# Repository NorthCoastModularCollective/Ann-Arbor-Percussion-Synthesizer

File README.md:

# Ann Arbor Percussion Synthesizer

A module that generates “abstract” percussion sounds and has a fairly simple interface. It won’t be intended to create “bass drums” or “snares” or “hi hats”, though it’ll probably be able to make things that approximate those sounds. It is raw, dirty, glitchy, lo-fi, and abstract. A Banksy interpretation of a Dali painting of industrial-steam-punk-Qbert. Interacting with it gives you a feeling of exploration and discovery with little emphasis on predictability and reproducibility. However, great care was taken to make the experience not feel like pure chaos and randomness. 

CAUTION: this project is still in development. There are many bugs and gaps. 

Audio Sample, [here](https://soundcloud.com/verzerren/ann-arbor-percussion-synthesizer-v-001-sound-sample)

https://github.com/NorthCoastModularCollective/Ann-Arbor-Percussion-Synthesizer/assets/6989685/e6aa8b81-97f8-49d5-8cca-bbeed19dbfc6

Hardware Overview:
- Teensy 4.1
- Teensy Audio Library
- Eurorack Trigger/Gate input

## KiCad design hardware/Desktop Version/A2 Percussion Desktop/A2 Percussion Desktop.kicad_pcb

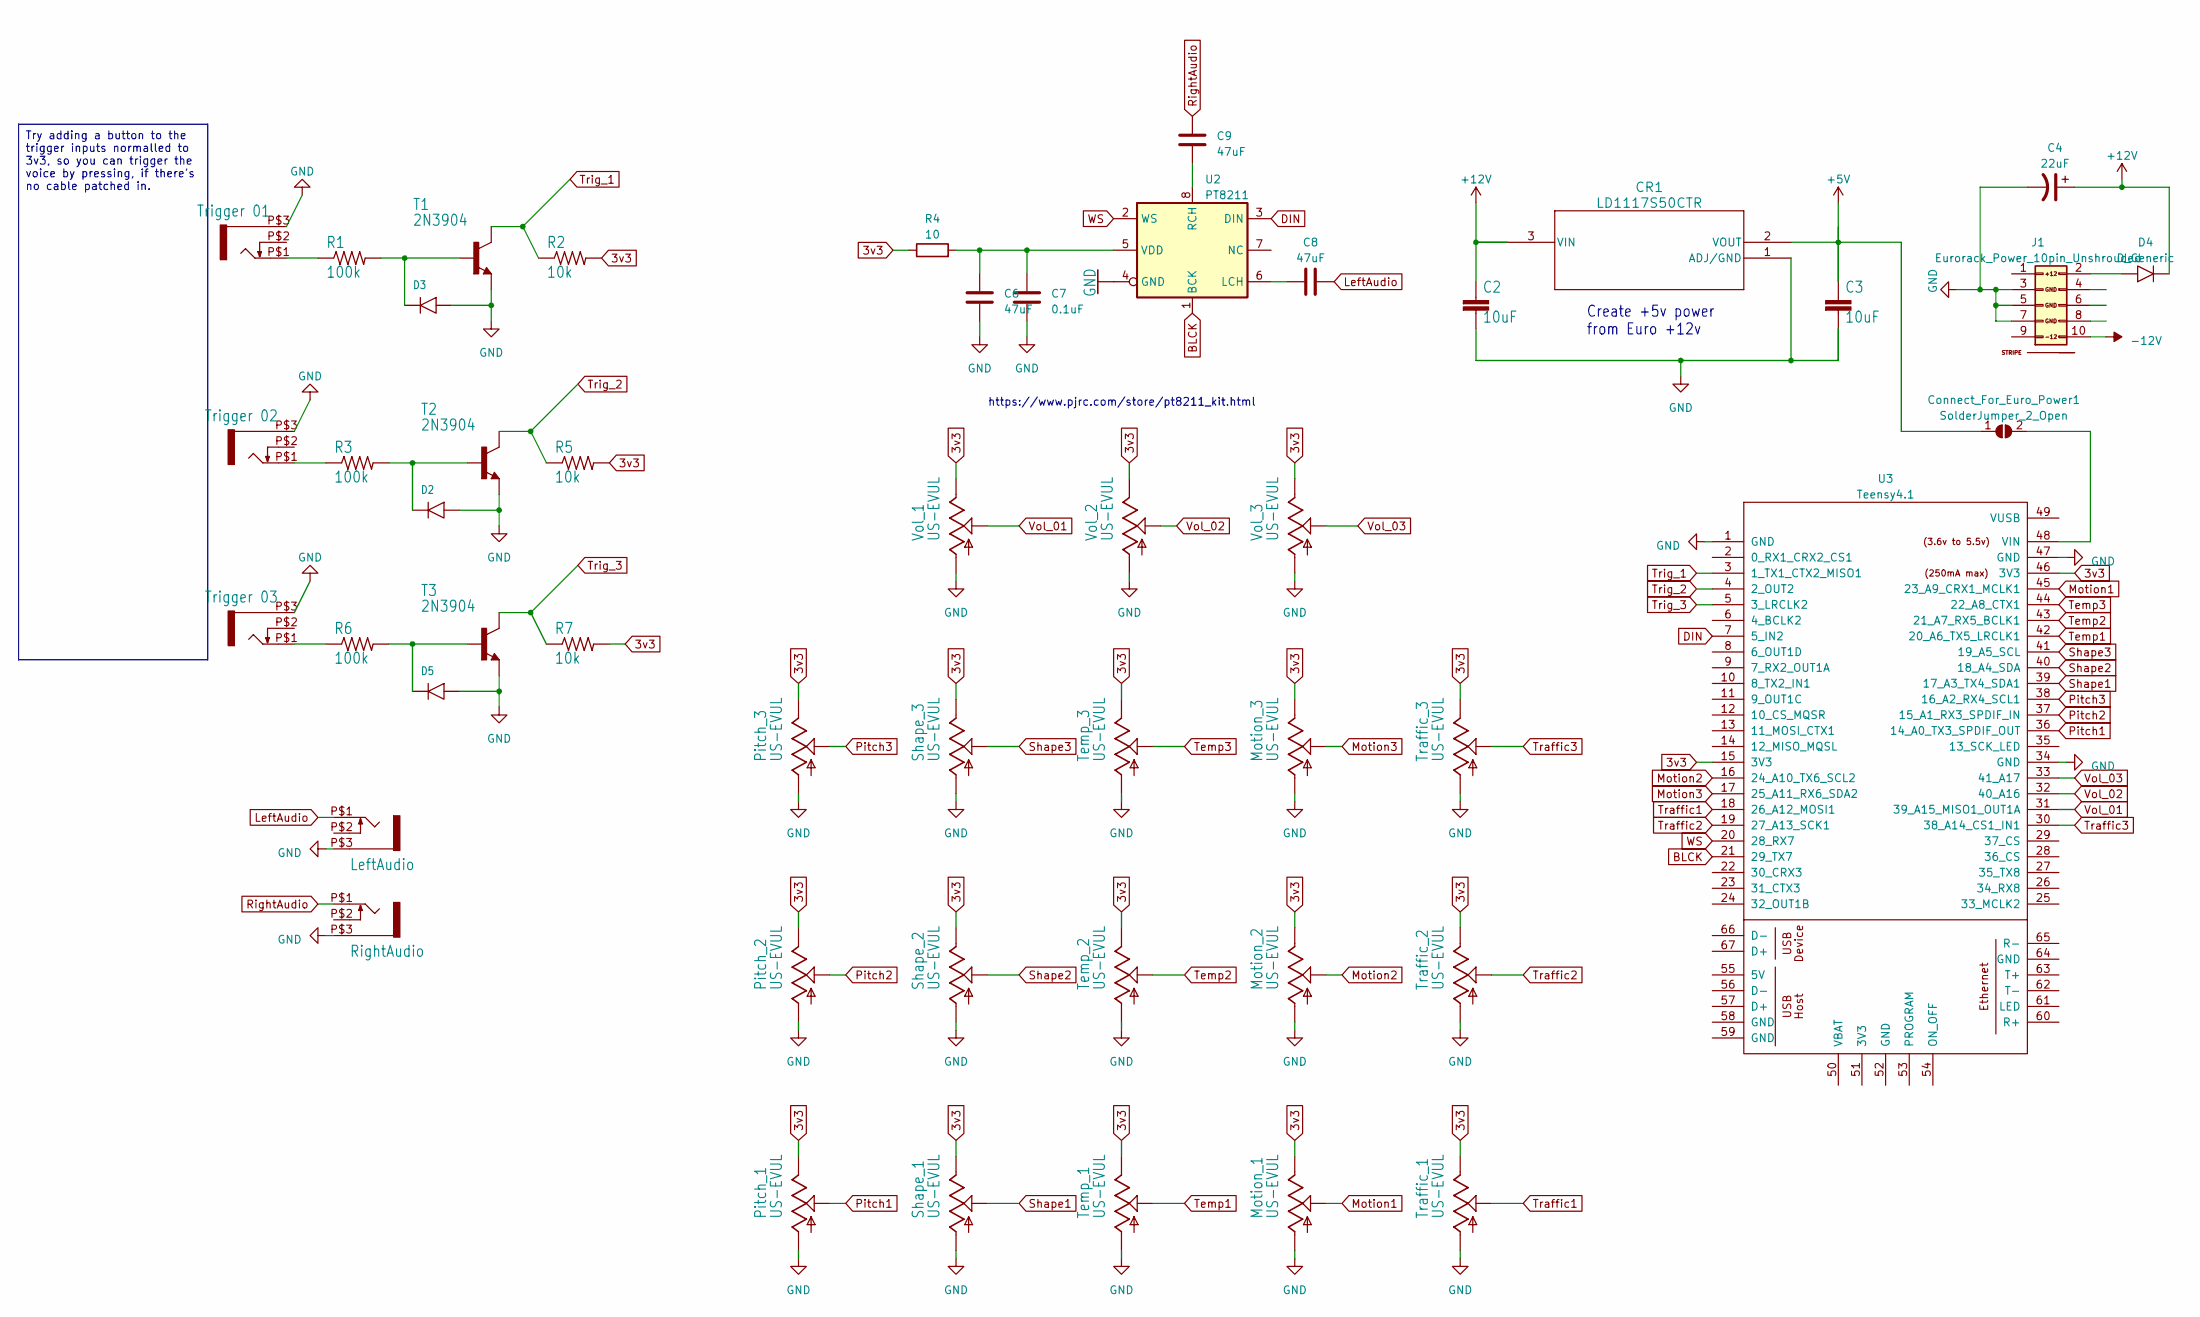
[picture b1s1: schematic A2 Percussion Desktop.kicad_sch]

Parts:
C2, C3: 10uF; C_Disc_D4.3mm_W1.9mm_P5.00mm
C4: 22uF; CP_Radial_D5.0mm_P2.50mm
C6, C8, C9: 47uF; C_Axial_L5.1mm_D3.1mm_P7.50mm_Horizontal
C7: 0.1uF; C_Axial_L5.1mm_D3.1mm_P7.50mm_Horizontal
CR1: LD1117S50CTR; SOT-223_STM
Connect_For_Euro_Power1: SolderJumper_2_Open; JUMPER_SMD_1x2
D2, D3, D5: DIODESOD-123; D_DO-35_P7.62mm_Horizontal
D4: D_Generic; D_DO-35_P7.62mm_Horizontal
J1: Eurorack_Power_10pin_Unshrouded; Pins_2x05_2.54mm_TH_Europower; Part Number 1-1002FBV0T
LeftAudio1: LeftAudio; WQP-PJ301M-12_JACK
Motion_1, Motion_2, Motion_3: US-EVUL; EVUFXL
Pitch_1, Pitch_2, Pitch_3: US-EVUL; EVUFXL
R1, R3, R6: 100k; R_Axial_DIN0207_L6.3mm_D2.5mm_P7.62mm_Horizontal
R2, R5, R7: 10k; R_Axial_DIN0207_L6.3mm_D2.5mm_P7.62mm_Horizontal
R4: 10; R_Axial_DIN0207_L6.3mm_D2.5mm_P7.62mm_Horizontal
RightAudio1: RightAudio; WQP-PJ301M-12_JACK
Shape_1, Shape_2, Shape_3: US-EVUL; EVUFXL
T1, T2, T3: 2N3904; TO92
TRIG1: Trigger 01; WQP-PJ301M-12_JACK
TRIG2: Trigger 02; WQP-PJ301M-12_JACK
TRIG3: Trigger 03; WQP-PJ301M-12_JACK
Temp_1, Temp_2, Temp_3: US-EVUL; EVUFXL
Traffic_1, Traffic_2, Traffic_3: US-EVUL; EVUFXL
U2: PT8211; VSSOP-8_3.0x3.0mm_P0.65mm
U3: Teensy4.1; Teensy41
Vol_1, Vol_2, Vol_3: US-EVUL; EVUFXL

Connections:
3v3: Motion_1.3 (E), Motion_2.3 (E), Motion_3.3 (E), Pitch_1.3 (E), Pitch_2.3 (E), Pitch_3.3 (E), R2.2, R4.1, R5.2, R7.2, Shape_1.3 (E), Shape_2.3 (E), Shape_3.3 (E), Temp_1.3 (E), Temp_2.3 (E), Temp_3.3 (E), Traffic_1.3 (E), Traffic_2.3 (E), Traffic_3.3 (E), U3.15 (3V3), U3.46 (3V3), Vol_1.3 (E), Vol_2.3 (E), Vol_3.3 (E)
+5V: C3.1, CR1.2 (VOUT), Connect_For_Euro_Power1.1 (A)
+12V: C2.1, C4.1, CR1.3 (VIN), D4.1 (K)
-12V: J1.10 (-12V)
BLCK: U2.1 (BCK), U3.21 (29_TX7)
DIN: U2.3 (DIN), U3.7 (5_IN2)
GND: C2.2, C3.2, C4.2, C6.2, C7.2, CR1.1 (ADJ/GND), D2.2 (A), D3.2 (A), D5.2 (A), J1.3 (GND), J1.5 (GND), J1.7 (GND), LeftAudio1.P$3 (1), Motion_1.1 (A), Motion_2.1 (A), Motion_3.1 (A), Pitch_1.1 (A), Pitch_2.1 (A), Pitch_3.1 (A), RightAudio1.P$3 (1), Shape_1.1 (A), Shape_2.1 (A), Shape_3.1 (A), T1.3 (E), T2.3 (E), T3.3 (E), TRIG1.P$3 (1), TRIG2.P$3 (1), TRIG3.P$3 (1), Temp_1.1 (A), Temp_2.1 (A), Temp_3.1 (A), Traffic_1.1 (A), Traffic_2.1 (A), Traffic_3.1 (A), U2.4 (GND), U3.1 (GND), U3.34 (GND), U3.47 (GND), Vol_1.1 (A), Vol_2.1 (A), Vol_3.1 (A)
LeftAudio: C8.2, LeftAudio1.P$1 (2)
Motion1: Motion_1.2 (S), U3.45 (23_A9_CRX1_MCLK1)
Motion2: Motion_2.2 (S), U3.16 (24_A10_TX6_SCL2)
Motion3: Motion_3.2 (S), U3.17 (25_A11_RX6_SDA2)
unnamed: Connect_For_Euro_Power1.2 (B), U3.48 (VIN)
unnamed: D2.1 (K), R3.2, T2.2 (B)
unnamed: D3.1 (K), R1.2, T1.2 (B)
unnamed: D4.2 (A), J1.2 (+12V)
unnamed: D5.1 (K), R6.2, T3.2 (B)
unnamed: R1.1, TRIG1.P$1 (2)
unnamed: R3.1, TRIG2.P$1 (2)
unnamed: R6.1, TRIG3.P$1 (2)
unnamed: C8.1, U2.6 (LCH)
unnamed: C9.1, U2.8 (RCH)
unnamed: C6.1, C7.1, R4.2, U2.5 (VDD)
Pitch1: Pitch_1.2 (S), U3.36 (14_A0_TX3_SPDIF_OUT)
Pitch2: Pitch_2.2 (S), U3.37 (15_A1_RX3_SPDIF_IN)
Pitch3: Pitch_3.2 (S), U3.38 (16_A2_RX4_SCL1)
RightAudio: C9.2, RightAudio1.P$1 (2)
Shape1: Shape_1.2 (S), U3.39 (17_A3_TX4_SDA1)
Shape2: Shape_2.2 (S), U3.40 (18_A4_SDA)
Shape3: Shape_3.2 (S), U3.41 (19_A5_SCL)
Temp1: Temp_1.2 (S), U3.42 (20_A6_TX5_LRCLK1)
Temp2: Temp_2.2 (S), U3.43 (21_A7_RX5_BCLK1)
Temp3: Temp_3.2 (S), U3.44 (22_A8_CTX1)
Traffic1: Traffic_1.2 (S), U3.18 (26_A12_MOSI1)
Traffic2: Traffic_2.2 (S), U3.19 (27_A13_SCK1)
Traffic3: Traffic_3.2 (S), U3.30 (38_A14_CS1_IN1)
Trig_1: R2.1, T1.1 (C), U3.3 (1_TX1_CTX2_MISO1)
Trig_2: R5.1, T2.1 (C), U3.4 (2_OUT2)
Trig_3: R7.1, T3.1 (C), U3.5 (3_LRCLK2)
Vol_01: U3.31 (39_A15_MISO1_OUT1A), Vol_1.2 (S)
Vol_02: U3.32 (40_A16), Vol_2.2 (S)
Vol_03: U3.33 (41_A17), Vol_3.2 (S)
WS: U2.2 (WS), U3.20 (28_RX7)

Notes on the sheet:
Try adding a button to the trigger inputs normalled to 3v3, so you can trigger the voice by pressing, if there's no cable patched in.
Create +5v power from Euro +12v
https://www.pjrc.com/store/pt8211_kit.html

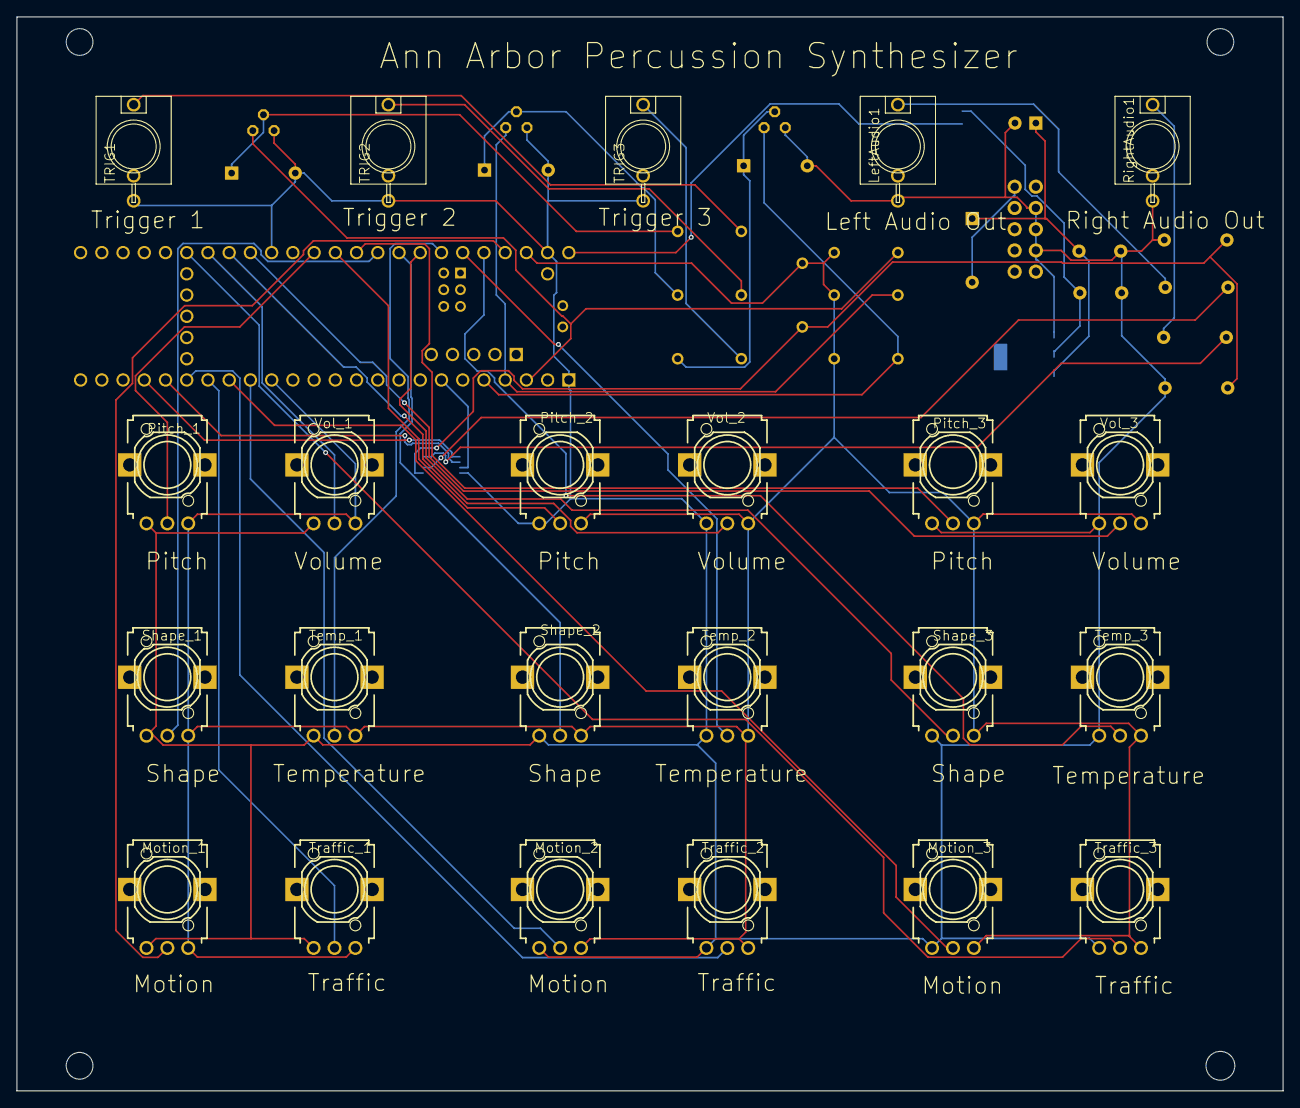
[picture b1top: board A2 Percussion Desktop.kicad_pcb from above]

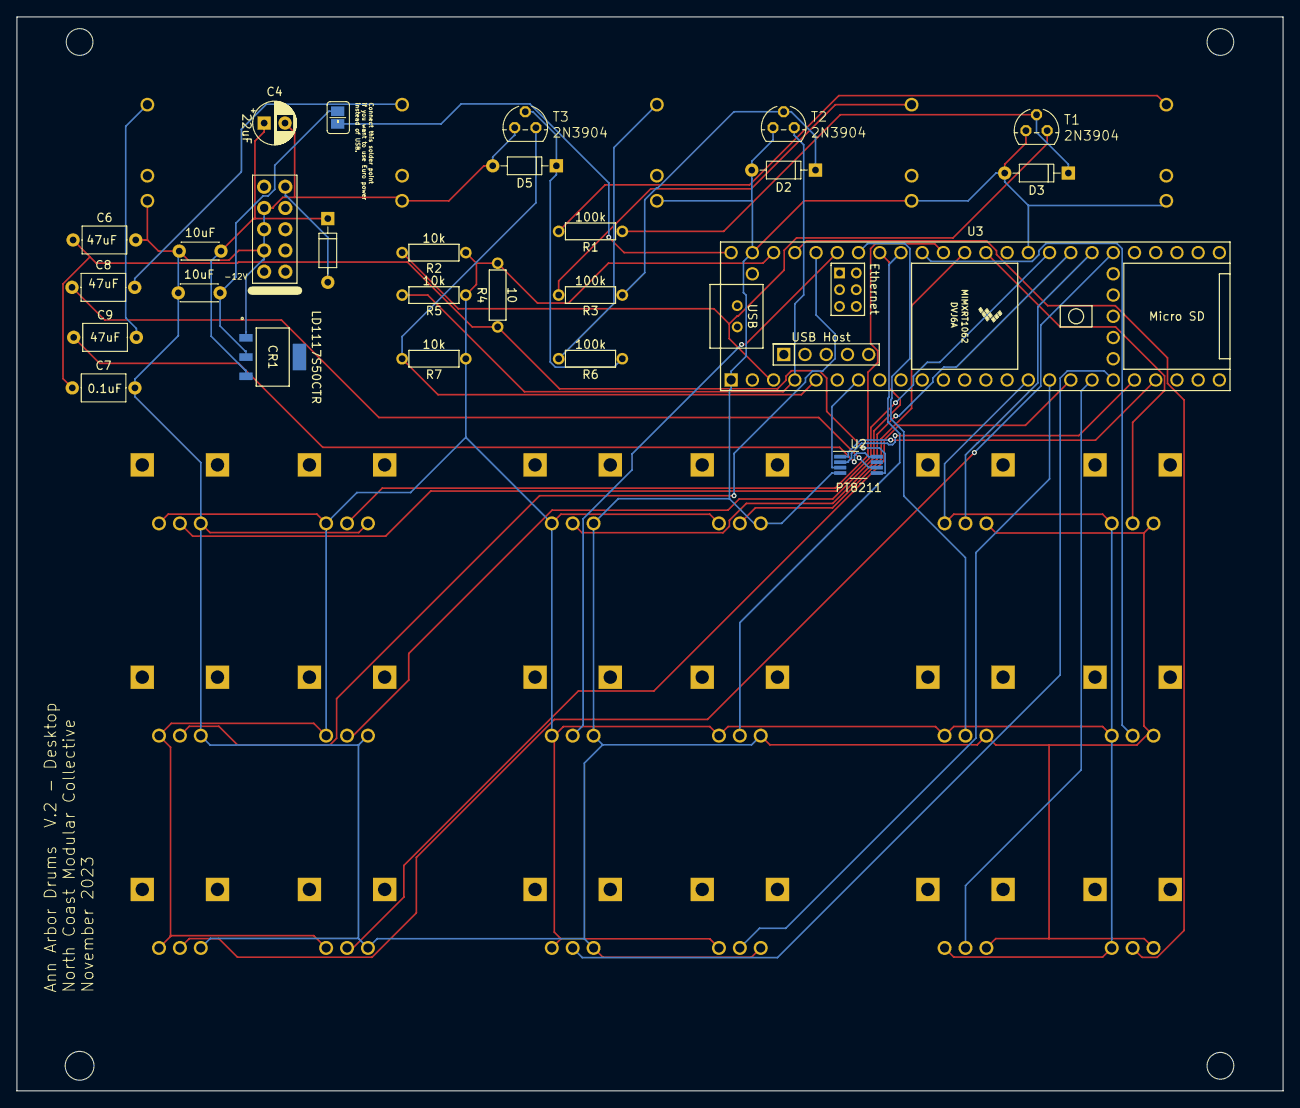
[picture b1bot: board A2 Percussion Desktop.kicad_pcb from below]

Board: 2 copper layers, 151.5 x 128.5 mm, 49 parts (26 on the bottom side), 41 nets.

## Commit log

2017-07-13 Unfinished Alpha Code - WORK IN PROGRESS
2017-07-13 Version .001 - WORK IN PROGRESS
    An alpha version of the board. Work in progress.
2017-07-15 Added link to audio sample
2023-11-12 Starting back over with version 1 and will rebuild up from there
    after a long hiatus, going to try and pick this one back up again. Restarting from an earlier version because some of the later versions had a lot of experiments that were me not knowing what I was d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
2023-11-12 Set up a bare basic test/validation script for Teensy and audio board to test for health
2023-11-12 Reverted back to a very old version of the code. This is super duper bad code. Don't use it yet.
2023-11-15 V2 of hardware and made a version of the software that uses the pt8211 chip for audio
2023-11-28 more small updates
2024-02-01 Updated pins for desktop hardware in code
    Set the pins in the old code to the new desktop hardware pins for the first voice.
